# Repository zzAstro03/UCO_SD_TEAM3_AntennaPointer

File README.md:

# UCO_SD_TEAM3_AntennaPointer

## Purpose
  This project was created for senior engineering design at the University of Central Oklahoma.
  Working with the FAA, the device is to aid in the installation of antennas by replacing
  a plumb bob and compass with a single digital device. This will save time and money.

## Design
  ...

## Goals
  For the first semester, the goal was to primarily get a physical design started and all of the individual electrical components working 
  at a basic level. We were successful.

  The goal for this semester is to finalize the device. Currently, the custom keypad PCB has been created, soldered, and programmed.
  A rudimentary GUI has been programmed to the display and allows the user to interact with it via the keypad. This allows
  the user to input the latitude, longitude, antenna offset, and date. The user is then able to hit enter, which will
  put them onto the outputs screen, where the current device Azimuth and Elevation are displayed.

  The next steps are to calibrate the IMU we are using. The magnetometer needs to adjust for hard and soft iron offsets, as well
  as tilt. Currently the elevation is reading pretty accurately.

  After the calibration is done, the user inputs will be used to calculate the magnetic declination and adjust the sensor data
  accordingly. The magnetic declination will adjust the azimuth readings, while the antenna offset wiill adjust the elevation readings.
  This adjusted data is what will then be put on the outputs screen as described above.

  After that, the device will be finished on the electrical side. I would like to do some quality of life improvements if I can get there.

  The mechanical design is focusing on the shell for the device, the silicone keys to protect the PCB keypad and waterproof the device,
  and creating a clamp that can attach to the side or back of an antenna to mount the device on.
  
## Components
### ESP32-S3-DevKitC-1 v1.1 (WORKING)
  This is the main brain of the entire device. It is a microcontroller capable of controlling
  various peripherals. It was chosen due to its widespread support and low power consumption.
  It is currently being programmed via ESP-IDF v5.4.0 with a majority of the code being written in C.

  Part:
  https://www.adafruit.com/product/5312
  <br />
  Datasheet:
  [https://docs.espressif.com/projects/esp-idf/en/stable/esp32s3/hw-reference/esp32s3/user-guide-devkitc-1.html](https://docs.espressif.com/projects/esp-dev-kits/en/latest/esp32s3/esp32-s3-devkitc-1/user_guide.html)
  <br />
  ESP-IDF v5.4.0:
  https://docs.espressif.com/projects/esp-idf/en/v5.4/esp32/get-started/index.html

### Adafruit TDK Invensense ICM20948 (WORKING, NOT IMPLEMENTED, NEEDS CALIBRATION)
  The orientation of the device is determined by an ICM20948. This is a 9 degree of freedom inertial
  measurement unit that includes an accelerometer, gyroscope, and magnetometer. By using the data
  output from this sensor, the device's orientation can be determined.

  Part:
  https://www.adafruit.com/product/4554
  <br />
  Datasheet:
  https://invensense.tdk.com/wp-content/uploads/2016/06/DS-000189-ICM-20948-v1.3.pdf

### World Magnetic Model (WORKING, NOT IMPLEMENTED)
  The World Magnetic Model is used to determine the magnetic declination of the device based on
  input latitude, longitude, date, and elevation. This magnetic declination is used to adjust the
  magnetometer readings to give a True North heading. It is updated every 5 years and was just recently
  updated in December of 2024. This model will be accurate until December of 2029.

  In the future I will create a guide on how to update the WMM.COF files to allow the device to update
  the model to be used indefinitely, as long as the WMM keeps updating every 5 years.

  The website is given below to allow you to read up on it. It is widely used throughout the world
  and also has open source MIT Licensed software that can be used.

  World Magnetic Model:
  https://www.ncei.noaa.gov/products/world-magnetic-model

### ILI9488 TFT LCD Display (WORKING)
  The ILI9488 thin-film-transistor liquid-crystal display is used to display output data and allow
  the user to interact with the device via the keypad. A driver was downloaded from the atanisoft
  component via the ESP-IDF Component Registry. The driver is responsible for lower level stuff 
  like drawing pixels and communicating with the ESP32. This driver was then registered to be used via LVGL.

  Part:
  https://a.co/d/5So4UNi
  <br />
  Datasheet:
  https://www.hpinfotech.ro/ILI9488.pdf
  
### LVGL (WORKING, NEEDS BEAUTIFICATION)
  LVGL stands for Light and Versatile Graphics Library. It is an embedded graphics API and library and is the 
  primary tool in creating the GUI for the device. While the display driver draws pixels, this creates entire 
  pre-made widgets that can do a lot of cool stuff. It also allows me to easily implement the keypad navigation
  into the GUI as well. I won't go into extreme depth as there is a lot of documentation on their website.

  Documentation:
  https://docs.lvgl.io/master/index.html

### Keypad (WORKING)
  The keypad is a custom keypad created by yours truly. I designed the keypad in KiCad and had it sent to PCBWay to be created.
  <br />
  It is a matrix keypad that has the keys: 0 1 2 3 4 5 6 7 8 9 "." Enter Backspace Up Down Left Right
  <br />
  The primary use of this is to navigate the display's input and output screens. The input screen allows the 
  user to input the antenna offset as well as the necessary information to calculate magnetic declination. 
  The output screen displays the adjusted azimuth and elevation from the sensor.

  The circuit and PCB schematics are in the Design folder.

### Battery Management System (WORKING)
  The BMS chosen is a diymore 18650 battery shield. The battery shield controls the charging and
  IO state of the device. Two 18650 3500 mAh Li-ion batteries in parallel give the device a total
  7000 mAh. The battery life is still to be determined as the amp draw hasn't been measured yet.

  Shield:
  https://www.diymore.cc/products/18650-battery-shield-v8-mobile-power-bank-3v-5v-for-arduino-esp32-esp8266-wifi
  <br />
  Batteries:
  https://imrbatteries.com/products/samsung-35e-18650-3500mah-8a-battery

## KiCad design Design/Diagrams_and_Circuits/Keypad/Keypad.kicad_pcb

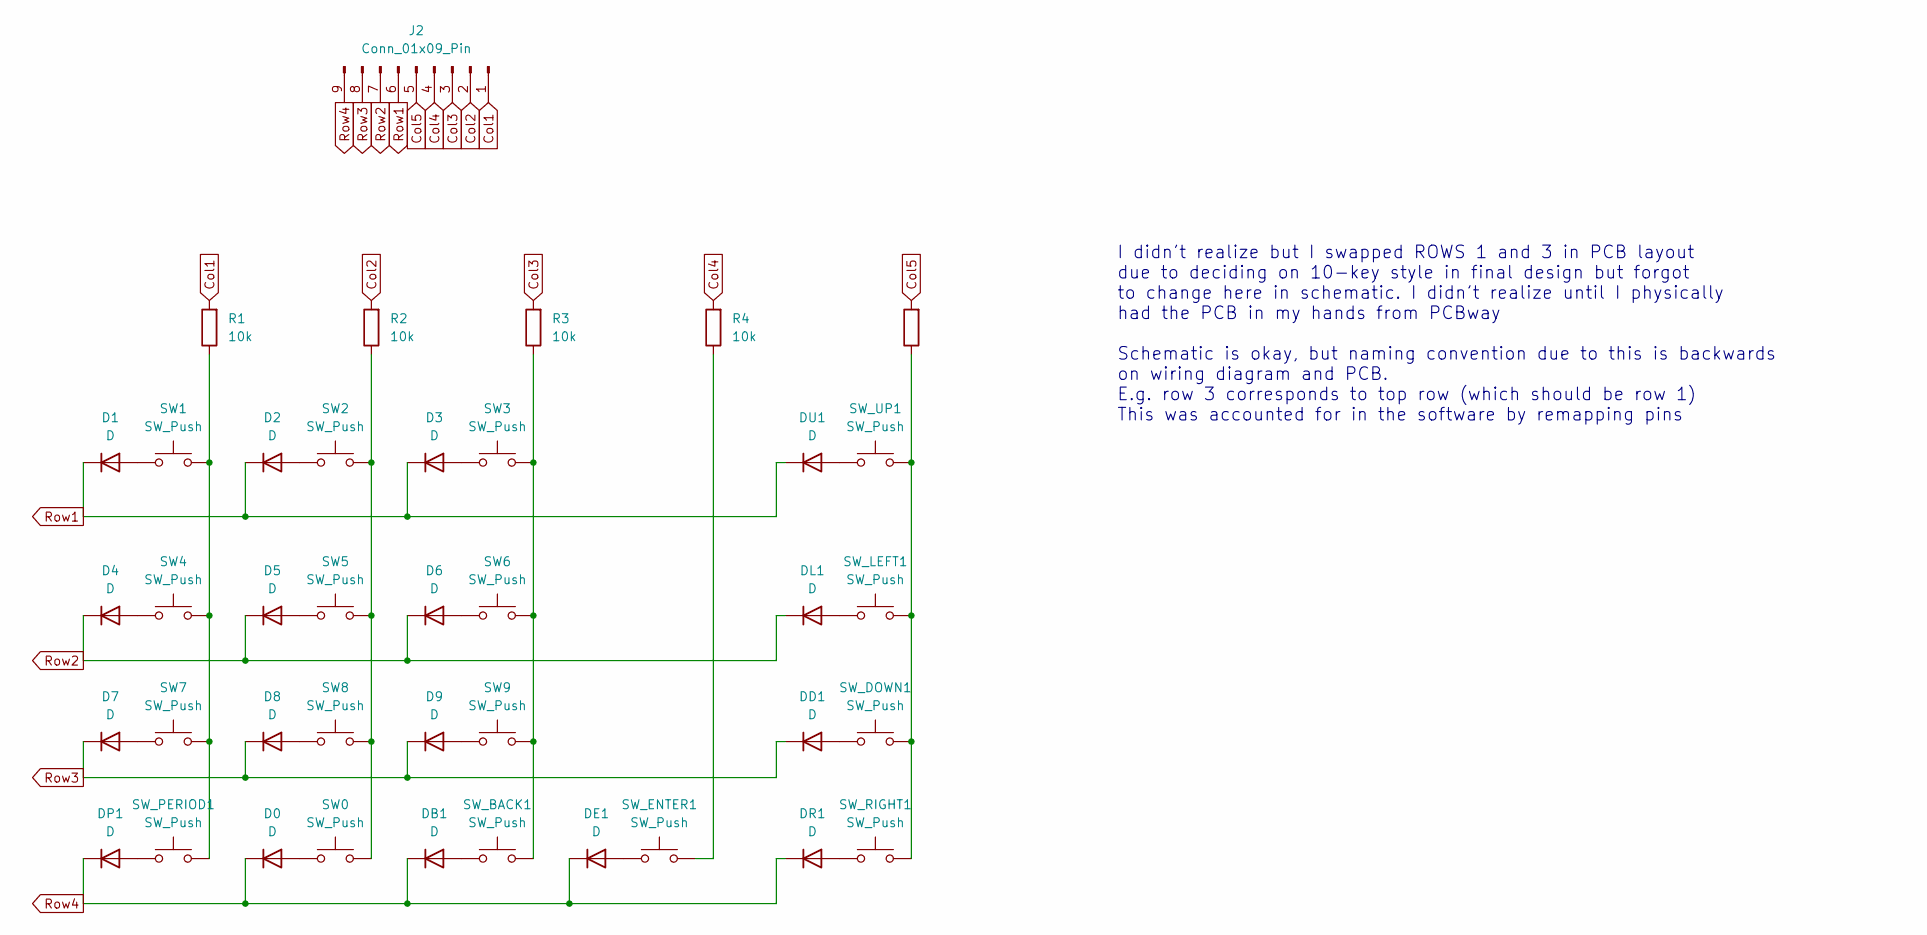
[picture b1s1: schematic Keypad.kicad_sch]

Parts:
D0, D1, D2, D3, D4, D5, D6, D7, D8, D9: D; D_DO-35_SOD27_P7.62mm_Horizontal
DB1: D; D_DO-35_SOD27_P7.62mm_Horizontal
DD1: D; D_DO-35_SOD27_P7.62mm_Horizontal
DE1: D; D_DO-35_SOD27_P7.62mm_Horizontal
DL1: D; D_DO-35_SOD27_P7.62mm_Horizontal
DP1: D; D_DO-35_SOD27_P7.62mm_Horizontal
DR1: D; D_DO-35_SOD27_P7.62mm_Horizontal
DU1: D; D_DO-35_SOD27_P7.62mm_Horizontal
J2: Conn_01x09_Pin; PinHeader_1x09_P2.54mm_Vertical
R1, R2, R3, R4, R5: 10k; R_Axial_DIN0204_L3.6mm_D1.6mm_P5.08mm_Horizontal
SW0, SW1, SW2, SW3, SW4, SW5, SW6, SW7, SW8, SW9: SW_Push; SW_PUSH-12mm
SW_BACK1: SW_Push; SW_PUSH-12mm
SW_DOWN1: SW_Push; SW_PUSH_6mm
SW_ENTER1: SW_Push; SW_PUSH-12mm
SW_LEFT1: SW_Push; SW_PUSH_6mm
SW_PERIOD1: SW_Push; SW_PUSH-12mm
SW_RIGHT1: SW_Push; SW_PUSH_6mm
SW_UP1: SW_Push; SW_PUSH_6mm

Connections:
Col1: J2.1, R1.2
Col2: J2.2, R2.2
Col3: J2.3, R3.2
Col4: J2.4, R4.2
Col5: J2.5, R5.2
unnamed: D0.2 (A), SW0.1
unnamed: D1.2 (A), SW1.1
unnamed: D2.2 (A), SW2.1
unnamed: D3.2 (A), SW3.1
unnamed: D4.2 (A), SW4.1
unnamed: D5.2 (A), SW5.1
unnamed: D6.2 (A), SW6.1
unnamed: D7.2 (A), SW7.1
unnamed: D8.2 (A), SW8.1
unnamed: D9.2 (A), SW9.1
unnamed: DB1.2 (A), SW_BACK1.1
unnamed: DD1.2 (A), SW_DOWN1.1
unnamed: DE1.2 (A), SW_ENTER1.1
unnamed: DL1.2 (A), SW_LEFT1.1
unnamed: DP1.2 (A), SW_PERIOD1.1
unnamed: DR1.2 (A), SW_RIGHT1.1
unnamed: DU1.2 (A), SW_UP1.1
unnamed: R1.1, SW1.2, SW4.2, SW7.2, SW_PERIOD1.2
unnamed: R2.1, SW0.2, SW2.2, SW5.2, SW8.2
unnamed: R3.1, SW3.2, SW6.2, SW9.2, SW_BACK1.2
unnamed: R4.1, SW_ENTER1.2
unnamed: R5.1, SW_DOWN1.2, SW_LEFT1.2, SW_RIGHT1.2, SW_UP1.2
Row1: D1.1 (K), D2.1 (K), D3.1 (K), DU1.1 (K), J2.6
Row2: D4.1 (K), D5.1 (K), D6.1 (K), DL1.1 (K), J2.7
Row3: D7.1 (K), D8.1 (K), D9.1 (K), DD1.1 (K), J2.8
Row4: D0.1 (K), DB1.1 (K), DE1.1 (K), DP1.1 (K), DR1.1 (K), J2.9

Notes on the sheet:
I didn't realize but I swapped ROWS 1 and 3 in PCB layout due to deciding on 10-key style in final design but forgot to change here in schematic. I didn't realize until I physically had the PCB in my hands from PCBway Schematic is okay, but naming convention due to this is backwards on wiring diagr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

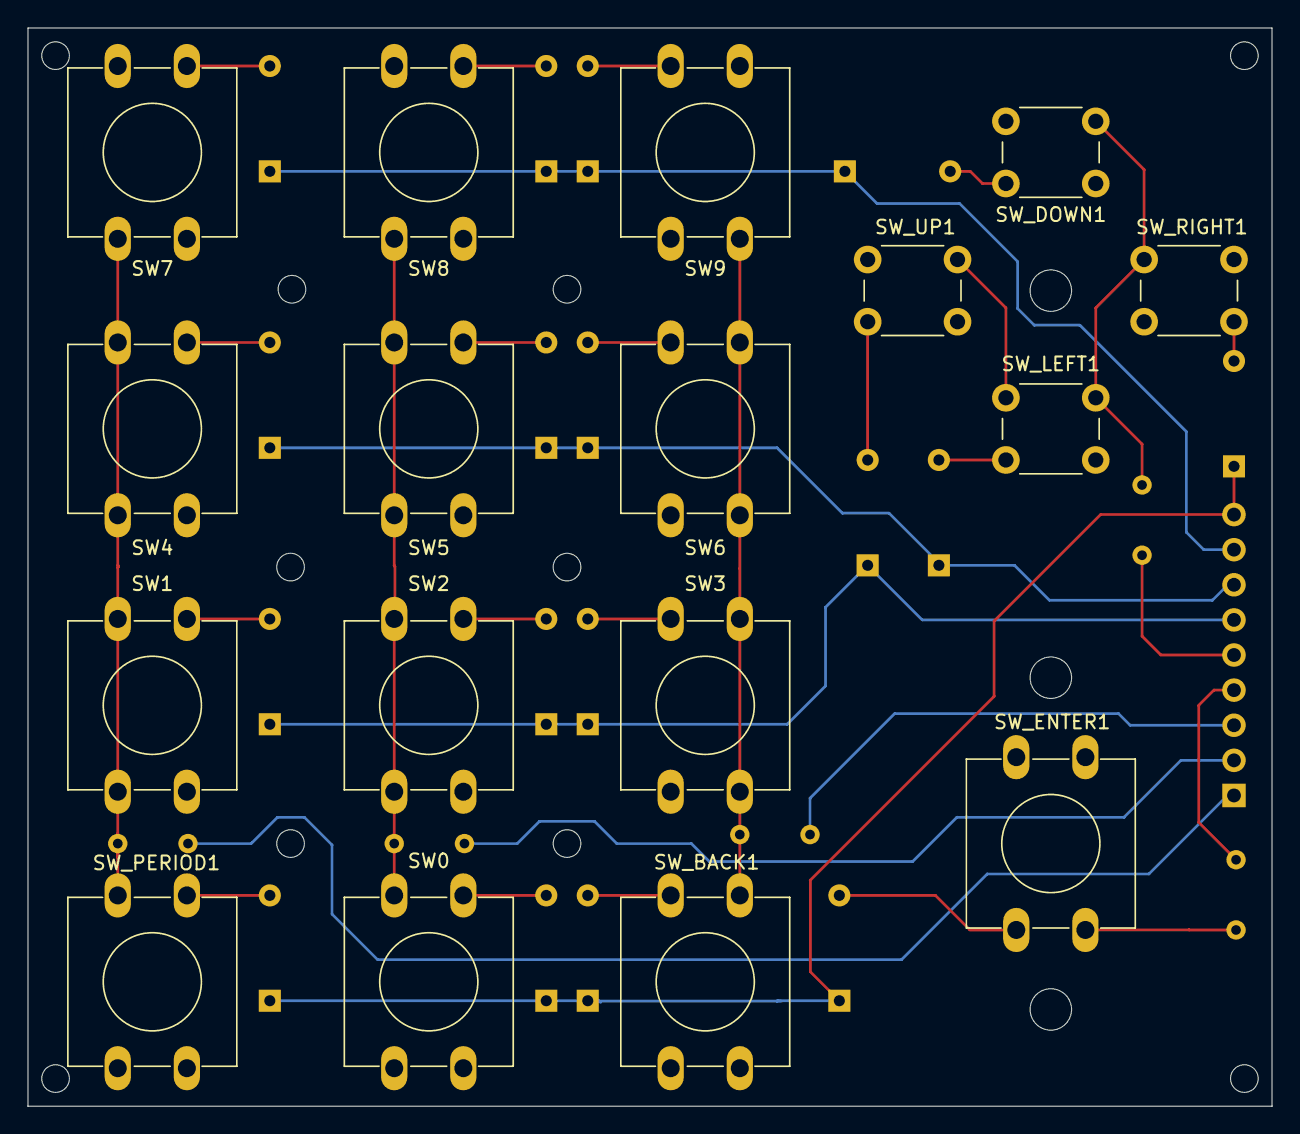
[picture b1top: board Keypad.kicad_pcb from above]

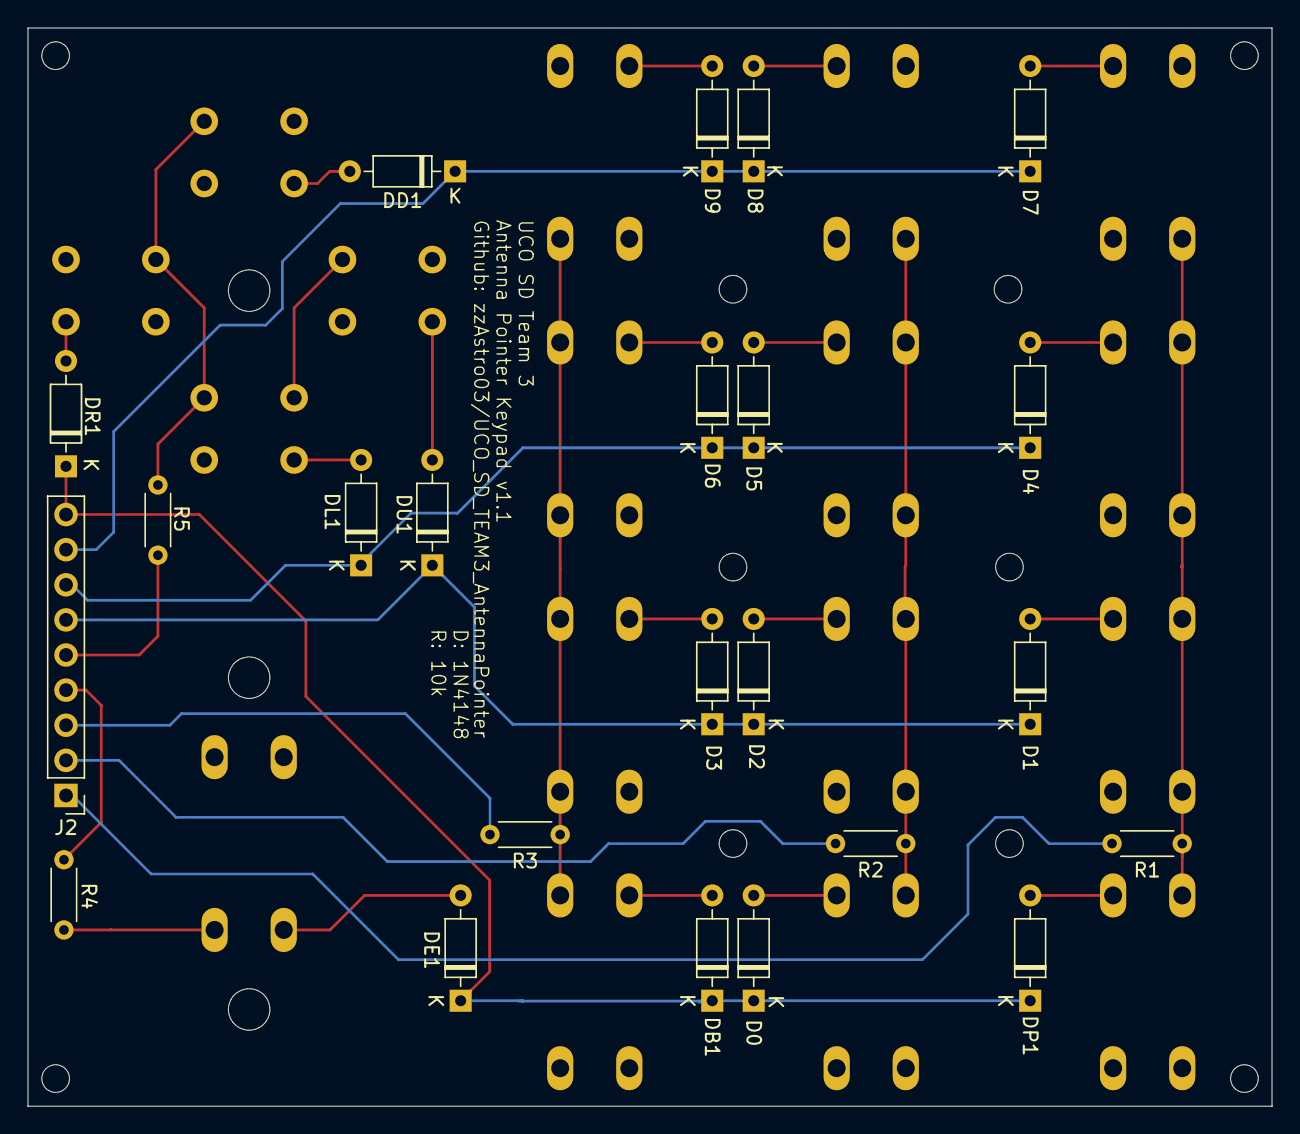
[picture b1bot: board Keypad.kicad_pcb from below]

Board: 2 copper layers, 90.0 x 78.0 mm, 40 parts (23 on the bottom side), 31 nets.

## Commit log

2025-02-24 Spring 2025 Semester 2 Update
2025-02-25 Create delete
2025-02-25 Rename Team3_AntennaPointer_FinalReport.pdf to Semester 1_Final Report.pdf
